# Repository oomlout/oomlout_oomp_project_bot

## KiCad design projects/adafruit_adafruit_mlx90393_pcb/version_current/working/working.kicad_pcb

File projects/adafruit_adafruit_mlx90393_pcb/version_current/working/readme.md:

# Adafruit-MLX90393-PCB by adafruit  
This is a harvested standardized copy of a project from github.  
The original project can be found at:  
https://github.com/adafruit/Adafruit-MLX90393-PCB  
Please consult that link for additional, details, files, and license information.  
Note: It was auto harvested and if the original repo had more than one board file or anything out of the ordinary the files here are likely not representative.

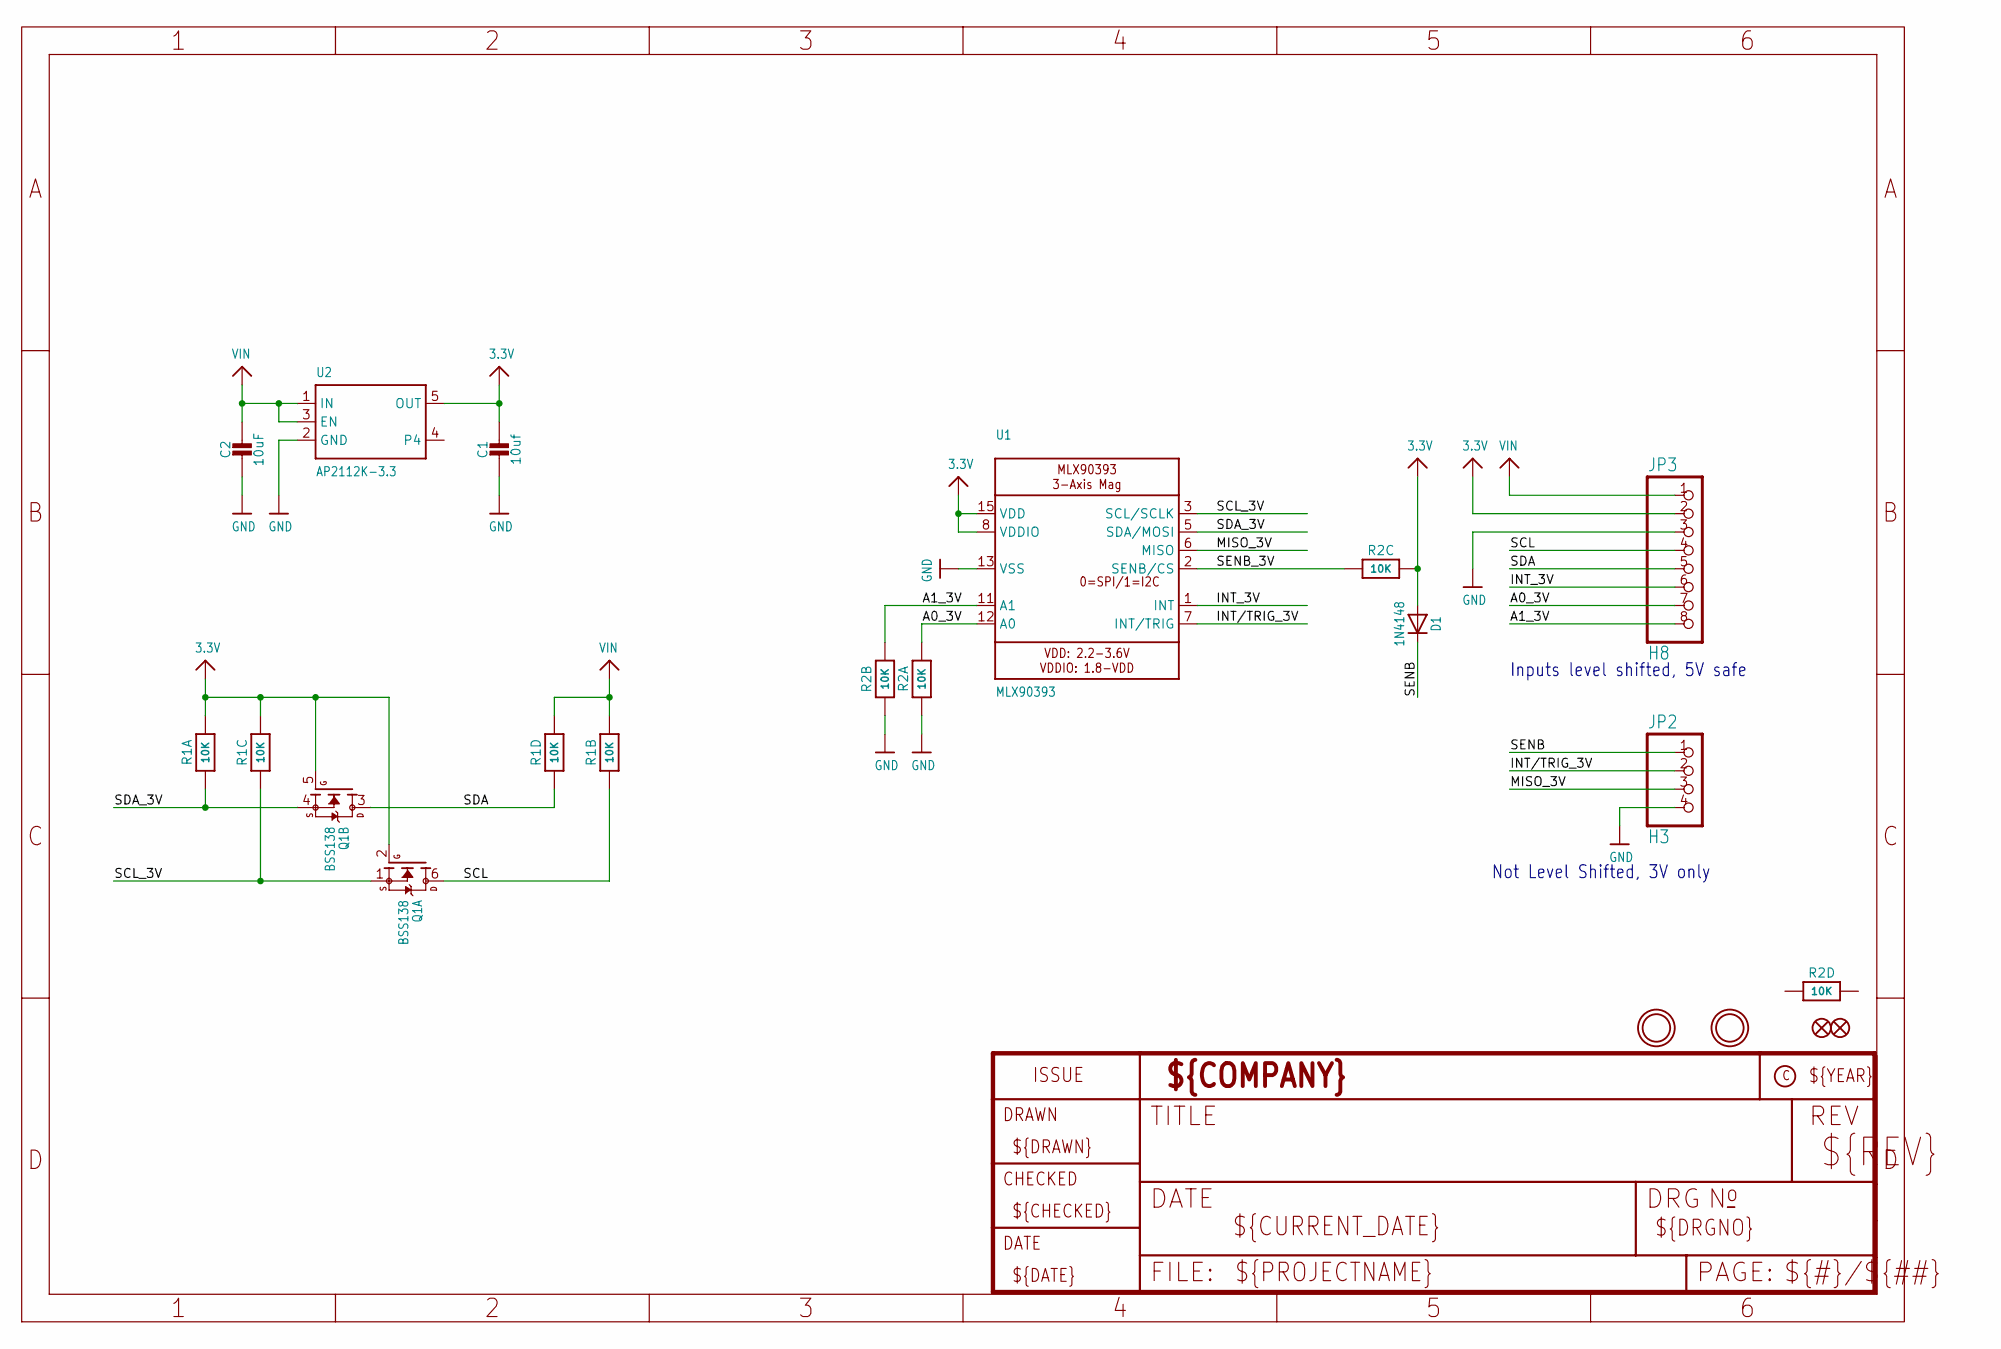
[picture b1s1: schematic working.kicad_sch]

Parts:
C1: 10uf; 0805_10MGAP
C2: 10uF; 0805_10MGAP
D1: 1N4148; SOD-323
FID1, FID3: FIDUCIAL_1MM
JP2: H3; 1X04_ROUND
JP3: H8; 1X08_ROUND
Q1: BSS138; SOT363
R1, R2: 10K; RESPACK_4X0603_NO
U1: MLX90393; QFN16_3MM
U2: AP2112K-3.3; SOT23-5
U$19, U$23: MOUNTINGHOLE2.5; MOUNTINGHOLE_2.5_PLATED

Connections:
3.3V: C1.1, D1.A, JP3.2, Q1.2 (G), Q1.5 (G), R1.6 (2), R1.8 (2), R2.6 (2), U1.8 (VDDIO), U1.15 (VDD), U2.5 (OUT)
A0_3V: JP3.7, R2.8 (2), U1.12 (A0)
A1_3V: JP3.8, R2.7 (2), U1.11 (A1)
GND: C1.2, C2.2, JP2.4, JP3.3, R2.1, R2.2 (1), U1.13 (VSS), U2.2 (GND)
INT/TRIG_3V: JP2.2, U1.7 (INT/TRIG)
INT_3V: JP3.6, U1.1 (INT)
MISO_3V: JP2.3, U1.6 (MISO)
SCL: JP3.4, Q1.6 (D), R1.2 (1)
SCL_3V: Q1.1 (S), R1.3 (1), U1.3 (SCL/SCLK)
SDA: JP3.5, Q1.3 (D), R1.4 (1)
SDA_3V: Q1.4 (S), R1.1, U1.5 (SDA/MOSI)
SENB: D1.C, JP2.1
SENB_3V: R2.3 (1), U1.2 (SENB/CS)
VIN: C2.1, JP3.1, R1.5 (2), R1.7 (2), U2.1 (IN), U2.3 (EN)

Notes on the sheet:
Not Level Shifted, 3V only~{}
Inputs level shifted, 5V safe~{}

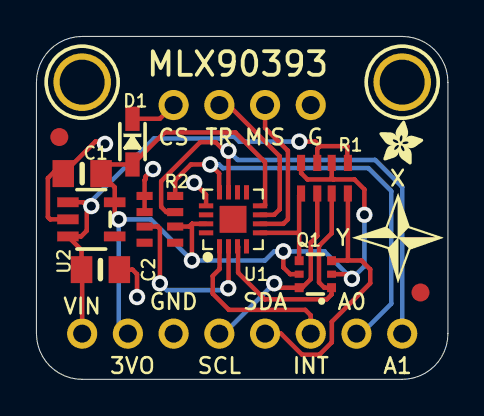
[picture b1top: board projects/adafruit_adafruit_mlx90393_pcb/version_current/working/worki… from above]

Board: 2 copper layers, 22.9 x 19.0 mm, 17 parts (1 on the bottom side), 14 nets.

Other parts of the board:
U$3: SYMBOL_COMPASSXY_5MM
U$18: PCBFEAT-REV-040
U$21: ADAFRUIT_2.5MM

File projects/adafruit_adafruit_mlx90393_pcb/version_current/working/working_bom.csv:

Row,Description,Part,References,Value,Footprint,Quantity Per PCB,Status,Datasheet
1,,CAP_CERAMIC0805_10MGAP,C1 C2,10uf,0805_10MGAP,2, ,
2,,DIODESOD-323,D1,1N4148,SOD-323,1, ,
3,,HEADER-1X4ROUND,JP2,H3,1X04_ROUND,1, ,
4,,HEADER-1X8ROUND,JP3,H8,1X08_ROUND,1, ,
5,,MOSFET-N_DUAL,Q1,BSS138,SOT363,1, ,
6,,RESISTOR_4PACK_NO,R1 R2,10K,RESPACK_4X0603_NO,2, ,
7,,VREG_SOT23-5,U2,AP2112K-3.3,SOT23-5,1, ,
8,,MLX90393,U1,MLX90393,QFN16_3MM,1, ,





Project info:
Schematic:,working
Variant:,default
Revision:,
Date:,2023-08-03_17-21-22
KiCad Version:,7.0.6-7.0.6~ubuntu22.04.1
Statistics:
Component Groups:,8
Component Count:,10 (0 SMD/ 0 THT)
Fitted Components:,10 (0 SMD/ 0 THT)
Number of PCBs:,1
Total Components:,10

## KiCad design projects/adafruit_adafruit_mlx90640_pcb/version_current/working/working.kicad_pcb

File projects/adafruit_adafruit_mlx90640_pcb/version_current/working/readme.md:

# Adafruit-MLX90640-PCB by adafruit  
This is a harvested standardized copy of a project from github.  
The original project can be found at:  
https://github.com/adafruit/Adafruit-MLX90640-PCB  
Please consult that link for additional, details, files, and license information.  
Note: It was auto harvested and if the original repo had more than one board file or anything out of the ordinary the files here are likely not representative.

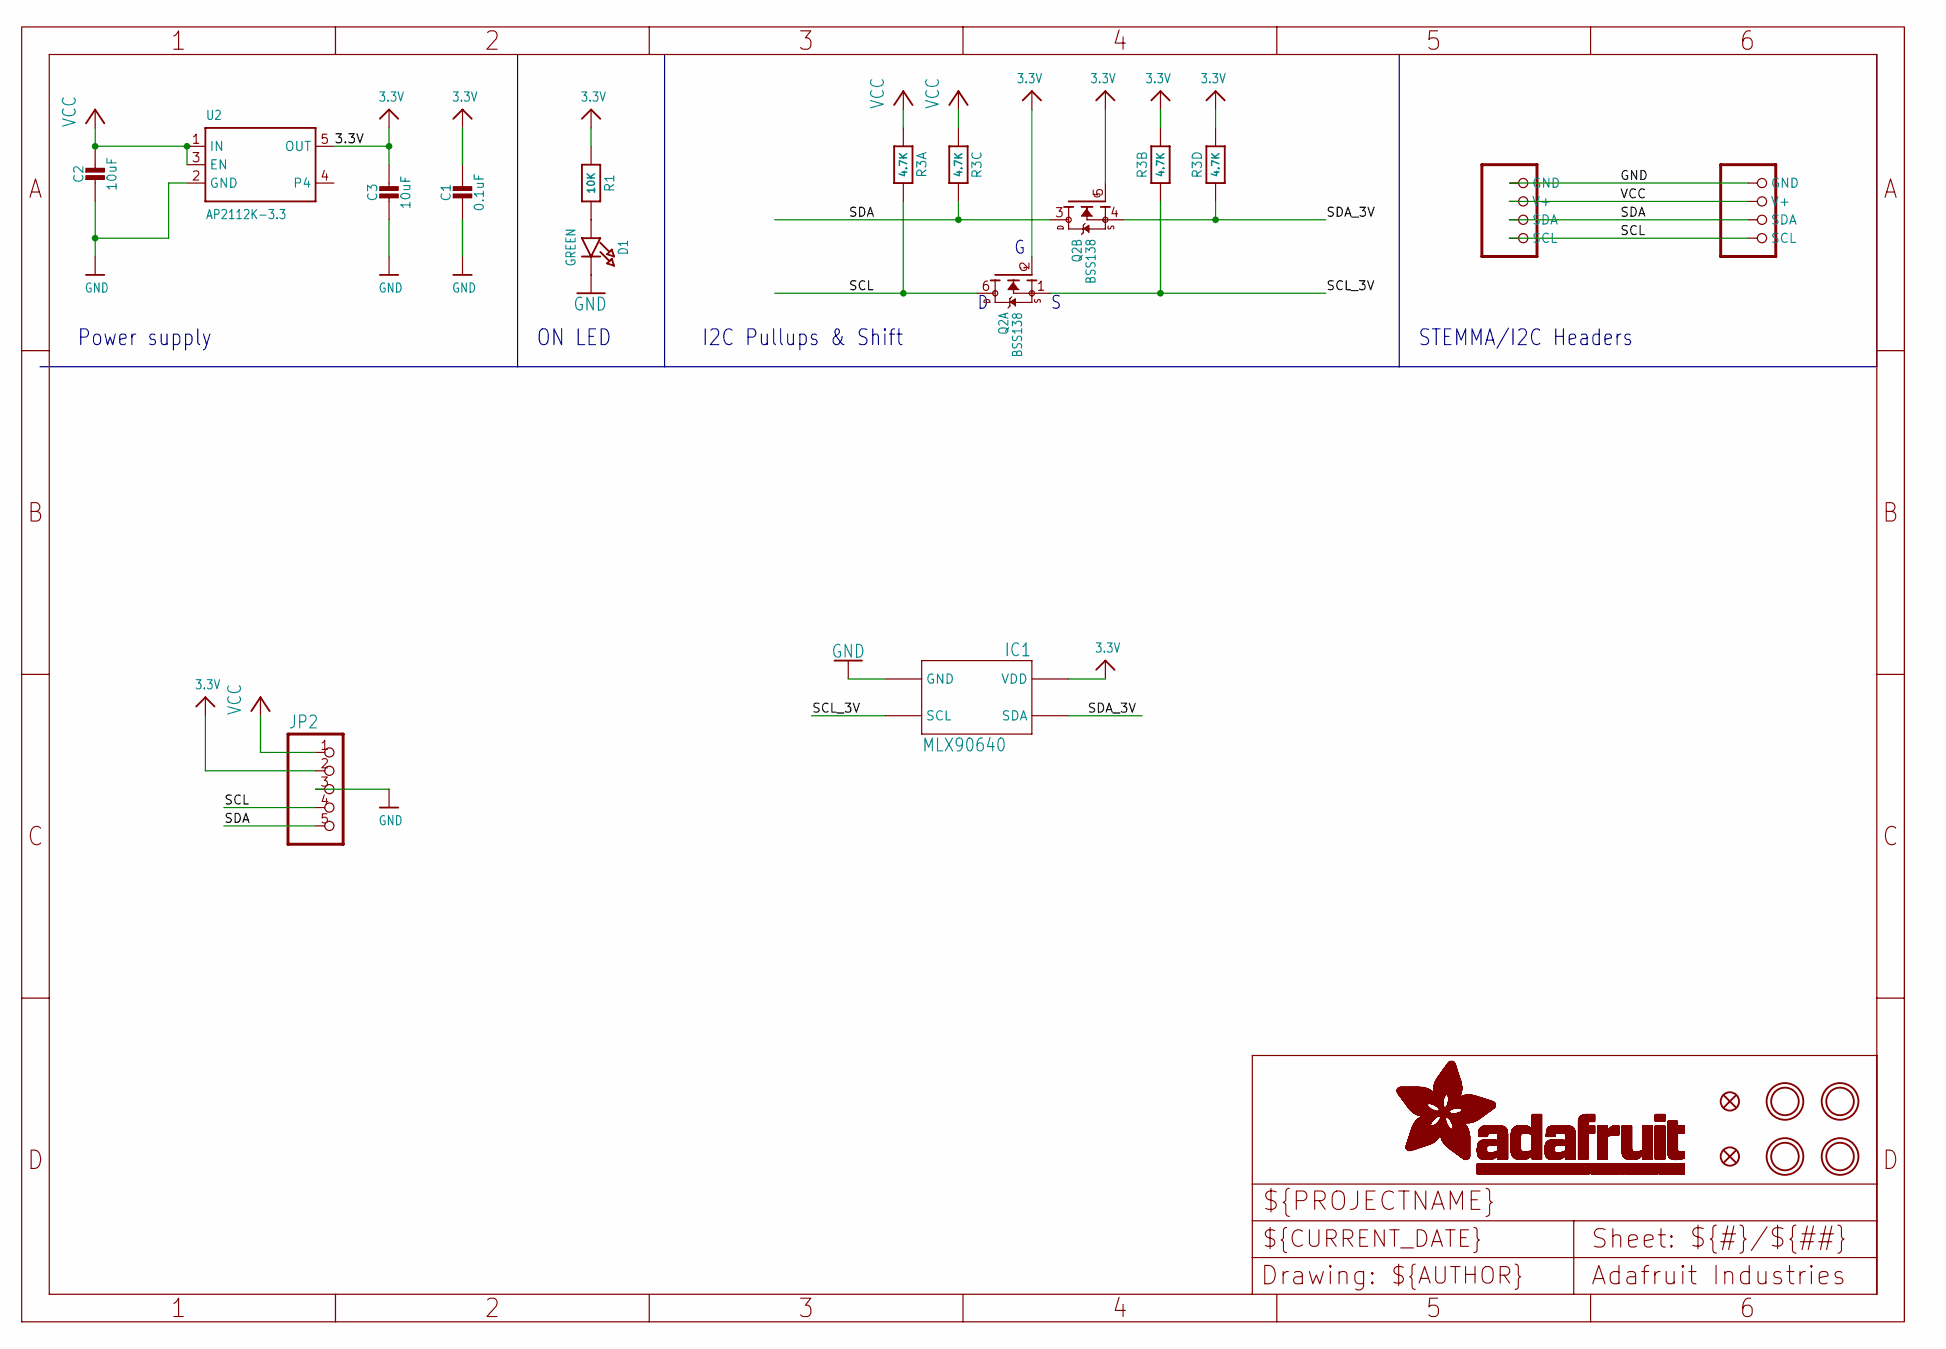
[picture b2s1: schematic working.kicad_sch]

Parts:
C1: 0.1uF; 0603-NO
C2, C3: 10uF; 0805-NO
CONN3, CONN4: STEMMA_I2C_QT; JST_SH4
D1: GREEN; CHIPLED_0603_NOOUTLINE
FID3, FID4: FIDUCIAL_1MM
IC1: MLX90640
JP2: HEADER-1X5ROUND; 1X05_ROUND
Q2: BSS138; SOT363
R1: 10K; 0603-NO
R3: 4.7K; RESPACK_4X0603
U2: AP2112K-3.3; SOT23-5
U$1, U$17, U$19, U$21: MOUNTINGHOLE2.5; MOUNTINGHOLE_2.5_PLATED

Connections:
3.3V: C1.1, C3.1, IC1.VDD, JP2.2, Q2.2 (G), Q2.5 (G), R1.1, R3.2 (1), R3.4 (1), U2.5 (OUT)
GND: C1.2, C2.2, C3.2, CONN3.1 (GND), CONN4.1 (GND), D1.C, IC1.GND, JP2.3, U2.2 (GND)
unnamed: D1.A, R1.2
SCL: CONN3.4 (SCL), CONN4.4 (SCL), JP2.4, Q2.6 (D), R3.8 (2)
SCL_3V: IC1.SCL, Q2.1 (S), R3.7 (2)
SDA: CONN3.3 (SDA), CONN4.3 (SDA), JP2.5, Q2.3 (D), R3.6 (2)
SDA_3V: IC1.SDA, Q2.4 (S), R3.5 (2)
VCC: C2.1, CONN3.2 (V+), CONN4.2 (V+), JP2.1, R3.1, R3.3 (1), U2.1 (IN), U2.3 (EN)

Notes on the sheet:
Power supply
I2C Pullups & Shift
STEMMA/I2C Headers
ON LED

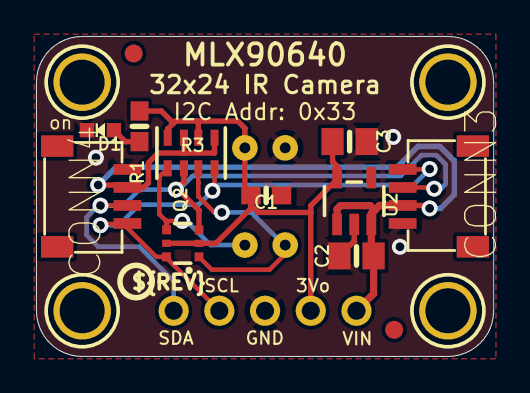
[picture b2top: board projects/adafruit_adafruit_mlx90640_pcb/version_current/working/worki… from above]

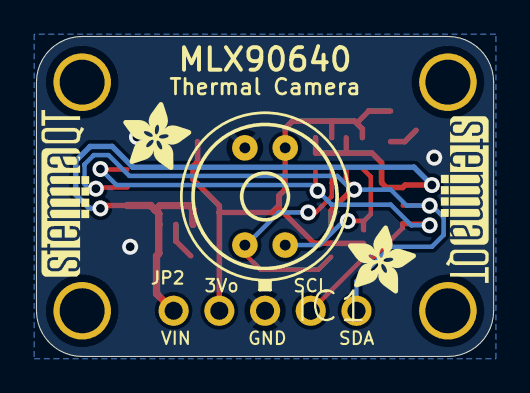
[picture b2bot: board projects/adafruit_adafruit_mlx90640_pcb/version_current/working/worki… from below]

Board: 2 copper layers, 25.4 x 17.8 mm, 23 parts (6 on the bottom side), 8 nets.

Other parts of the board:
U$4, U$22: ADAFRUIT_3.5MM
U$25: PCBFEAT-REV-040
U$30, U$31: STEMMAQT

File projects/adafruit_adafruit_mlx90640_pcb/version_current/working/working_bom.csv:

Row,Description,Part,References,Value,Footprint,Quantity Per PCB,Status,Datasheet
1,,CAP_CERAMIC0603_NO,C1,0.1uF,0603-NO,1, ,
2,,CAP_CERAMIC0805-NOOUTLINE,C2 C3,10uF,0805-NO,2, ,
3,,STEMMA_I2C_QT,CONN3 CONN4,STEMMA_I2C_QT,JST_SH4,2, ,
4,,LED0603_NOOUTLINE,D1,GREEN,CHIPLED_0603_NOOUTLINE,1, ,
5,,MLX90640,IC1,MLX90640,MLX90640,1, ,
6,,HEADER-1X5ROUND,JP2,HEADER-1X5ROUND,1X05_ROUND,1, ,
7,,MOSFET-N_DUAL,Q2,BSS138,SOT363,1, ,
8,,RESISTOR_4PACK,R3,4.7K,RESPACK_4X0603,1, ,
9,,RESISTOR_0603_NOOUT,R1,10K,0603-NO,1, ,
10,,VREG_SOT23-5,U2,AP2112K-3.3,SOT23-5,1, ,





Project info:
Schematic:,working
Variant:,default
Revision:,
Date:,2023-08-03_17-21-22
KiCad Version:,7.0.6-7.0.6~ubuntu22.04.1
Statistics:
Component Groups:,10
Component Count:,12 (0 SMD/ 0 THT)
Fitted Components:,12 (0 SMD/ 0 THT)
Number of PCBs:,1
Total Components:,12

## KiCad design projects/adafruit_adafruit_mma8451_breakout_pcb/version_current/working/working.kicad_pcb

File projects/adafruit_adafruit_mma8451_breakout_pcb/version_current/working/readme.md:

# Adafruit-MMA8451-Breakout-PCB by adafruit  
This is a harvested standardized copy of a project from github.  
The original project can be found at:  
https://github.com/adafruit/Adafruit-MMA8451-Breakout-PCB  
Please consult that link for additional, details, files, and license information.  
Note: It was auto harvested and if the original repo had more than one board file or anything out of the ordinary the files here are likely not representative.

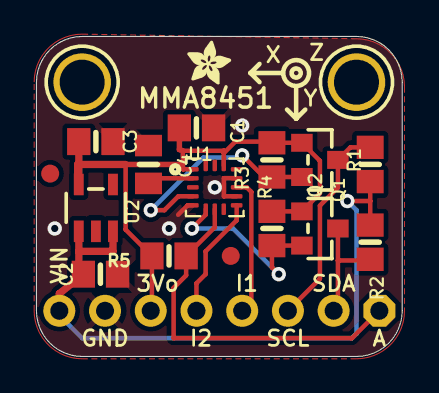
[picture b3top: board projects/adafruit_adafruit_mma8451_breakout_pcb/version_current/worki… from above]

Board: 2 copper layers, 20.3 x 17.8 mm, 19 parts (0 on the bottom side), 11 nets.

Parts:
C1: 0.1uF; 0805-NO
C2, C3: 10uF; 0805-NO
C4: 0.1uF; 0805_10MGAP
FID1, FID2: FIDUCIAL""; FIDUCIAL_1MM
JP1: 1X08_ROUND_70
Q1, Q2: BSS138; SOT23-WIDE
R1, R2, R3, R4, R5: 10K; 0805-NO
U1: MMA8451; MMA845X_QFN_16MM
U2: MIC5225-3.3; SOT23-5
U$3, U$6: MOUNTINGHOLE2.5; MOUNTINGHOLE_2.5_PLATED
U$10: ADAFRUIT_2.5MM

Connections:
+3V3: C1.1, C3.1, JP1.6, Q1.1, Q2.1, R3.2, R4.1, R5.2, U1.1, U1.14, U2.5
GND: C1.2, C2.2, C3.2, C4.2, JP1.7, U1.5, U1.10, U1.12, U2.2
INT1: JP1.4, U1.11
INT2: JP1.5, U1.9
unnamed: C4.1, U1.2
SA0: JP1.1, R5.1, U1.7
SCL: JP1.3, Q1.3, R1.1
SCL_3.3V: Q1.2, R3.1, U1.4
SDA: JP1.2, Q2.3, R2.2
SDA_3.3V: Q2.2, R4.2, U1.6
VIN: C2.1, JP1.8, R1.2, R2.1, U2.1, U2.3

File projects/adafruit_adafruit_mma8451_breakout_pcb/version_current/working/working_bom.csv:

Row,Description,Part,References,Value,Footprint,Quantity Per PCB,Status,Datasheet
1,,CAP_CERAMIC0805-NOOUTLINE,C1,0.1uF,0805-NO,1, ,
2,,CAP_CERAMIC0805_10MGAP,C4,0.1uF,0805_10MGAP,1, ,
3,,CAP_CERAMIC0805-NOOUTLINE,C2 C3,10uF,0805-NO,2, ,
4,,HEADER-1X870MIL,JP1,HEADER-1X870MIL,1X08_ROUND_70,1, ,
5,,MOSFET-NWIDE,Q1 Q2,BSS138,SOT23-WIDE,2, ,
6,,RESISTOR0805_NOOUTLINE,R1 R2 R3 R4 R5,10K,0805-NO,5, ,
7,,VREG_SOT23-5,U2,MIC5225-3.3,SOT23-5,1, ,
8,,ACCEL_MMA845X,U1,MMA8451,MMA845X_QFN_16MM,1, ,





Project info:
Schematic:,working
Variant:,default
Revision:,
Date:,2023-08-03_17-21-22
KiCad Version:,7.0.6-7.0.6~ubuntu22.04.1
Statistics:
Component Groups:,8
Component Count:,14 (0 SMD/ 0 THT)
Fitted Components:,14 (0 SMD/ 0 THT)
Number of PCBs:,1
Total Components:,14

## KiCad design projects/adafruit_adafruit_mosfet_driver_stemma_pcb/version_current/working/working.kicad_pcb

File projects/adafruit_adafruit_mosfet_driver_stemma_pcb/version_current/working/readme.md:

# Adafruit-MOSFET-Driver-STEMMA-PCB by adafruit  
This is a harvested standardized copy of a project from github.  
The original project can be found at:  
https://github.com/adafruit/Adafruit-MOSFET-Driver-STEMMA-PCB  
Please consult that link for additional, details, files, and license information.  
Note: It was auto harvested and if the original repo had more than one board file or anything out of the ordinary the files here are likely not representative.

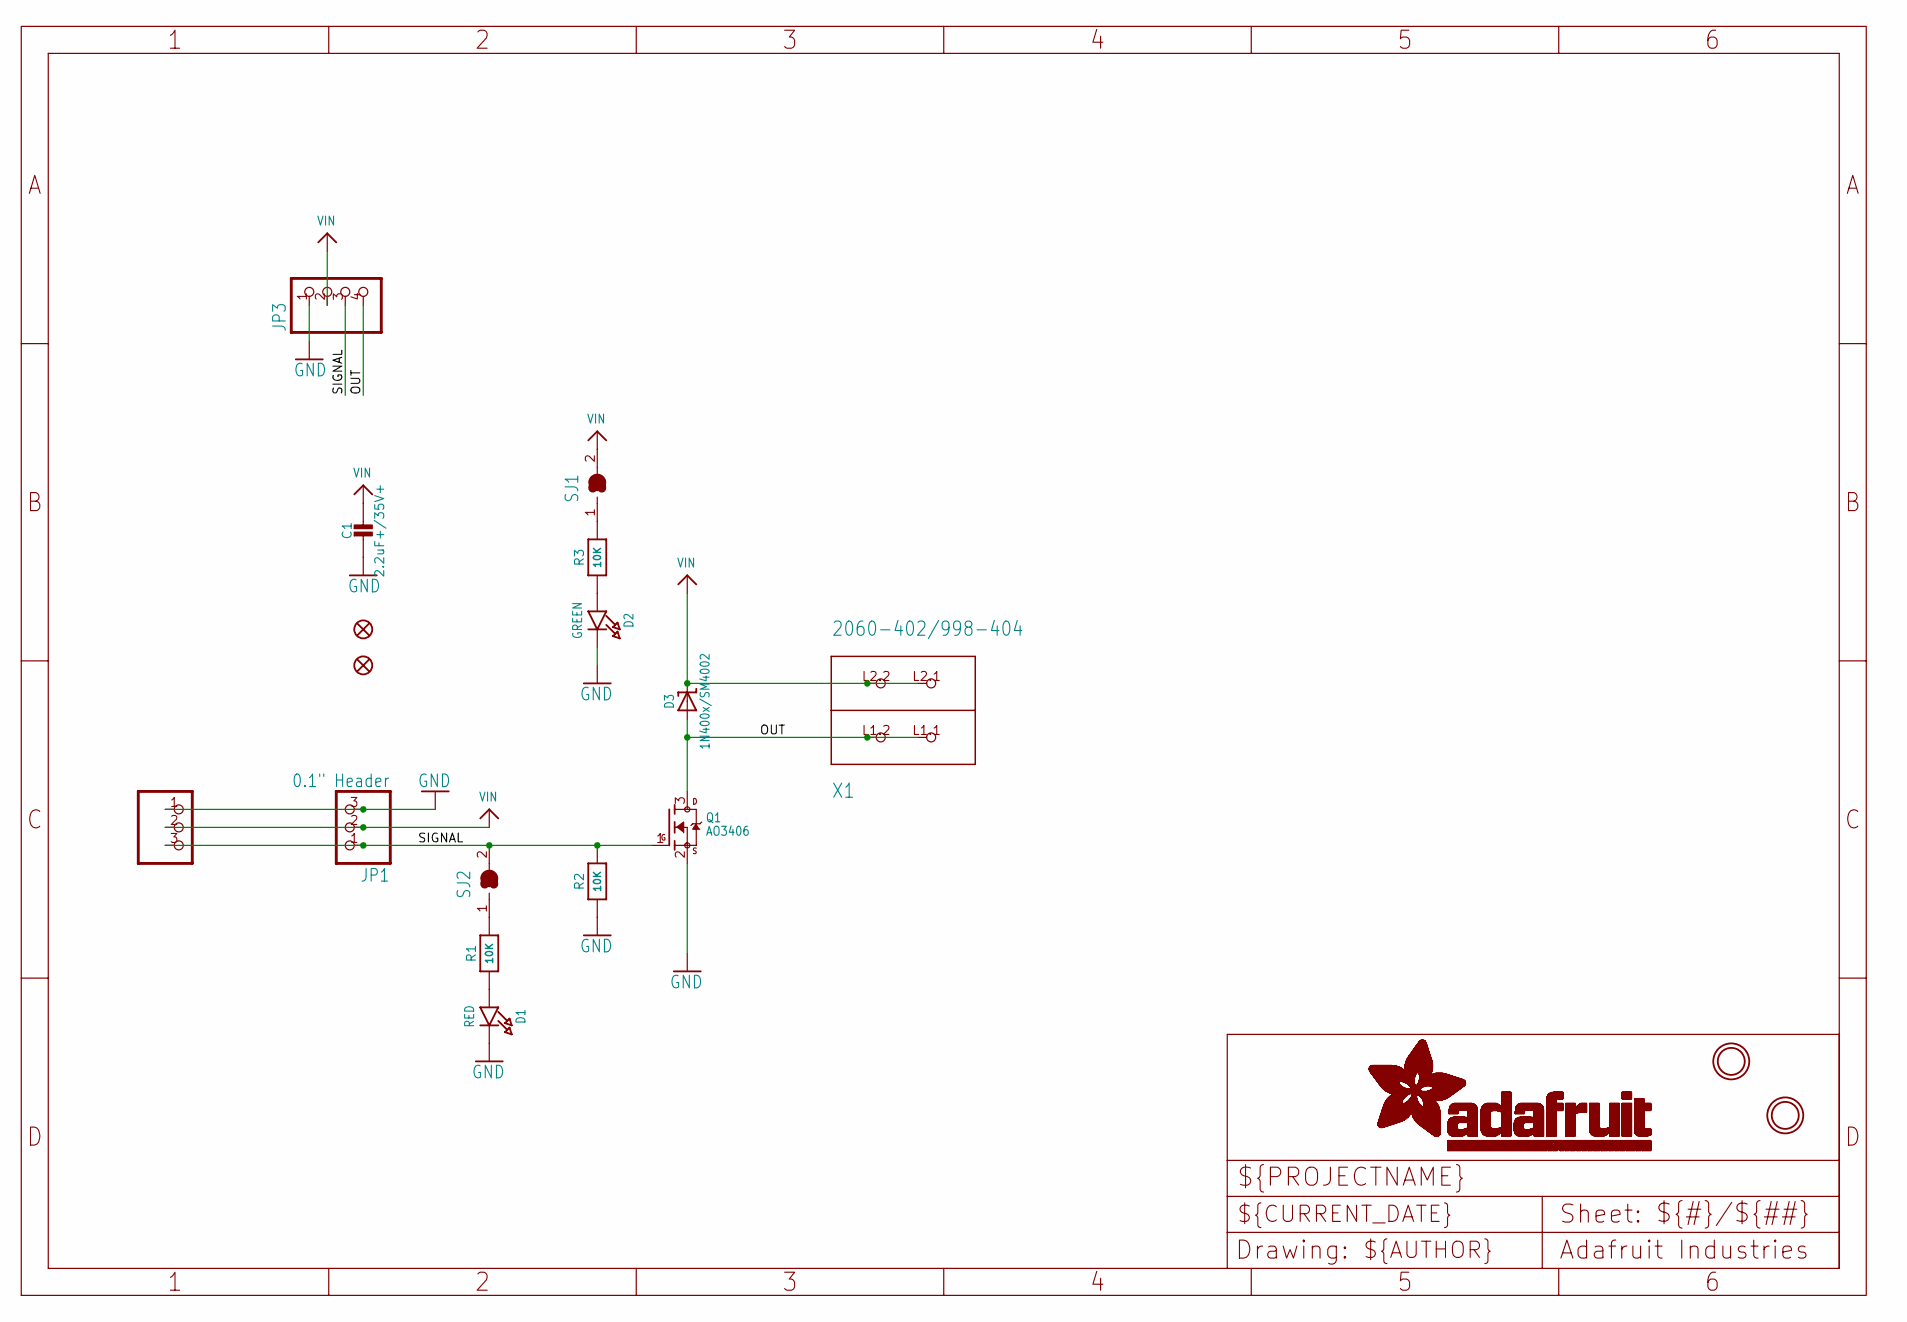
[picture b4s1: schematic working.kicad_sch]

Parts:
C1: 2.2uF+/35V+; 0805-NO
D1: RED; CHIPLED_0603_NOOUTLINE
D2: GREEN; CHIPLED_0603_NOOUTLINE
D3: 1N400x/SM4002; SOD-123
FID2, FID3: FIDUCIAL_1MM
JP1: 0.1" Header; 1X03_OVAL
JP3: HEADER-1X4ROUND; 1X04_ROUND
Q1: AO3406; SOT23-WIDE
R1, R2, R3: 10K; 0603-NO
SJ1, SJ2: SOLDERJUMPER_CLOSED; SOLDERJUMPER_CLOSEDWIRE
U$1, U$8: MOUNTINGHOLE2.5; MOUNTINGHOLE_2.5_PLATED
X1: 2060-402/998-404; P-2060-402_998-404
X4: JST PH 3; JSTPH3

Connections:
GND: C1.2, D1.C, D2.C, JP1.3, JP3.1, Q1.2 (S), R2.1, X4.1
unnamed: R3.2, SJ1.1
unnamed: D1.A, R1.1
unnamed: R1.2, SJ2.1
unnamed: D2.A, R3.1
OUT: D3.A, JP3.4, Q1.3 (D), X1.L1.1 (P1.1), X1.L1.2 (P1.2)
SIGNAL: JP1.1, JP3.3, Q1.1 (G), R2.2, SJ2.2, X4.3
VIN: C1.1, D3.C, JP1.2, JP3.2, SJ1.2, X1.L2.1 (P2.1), X1.L2.2 (P2.2), X4.2

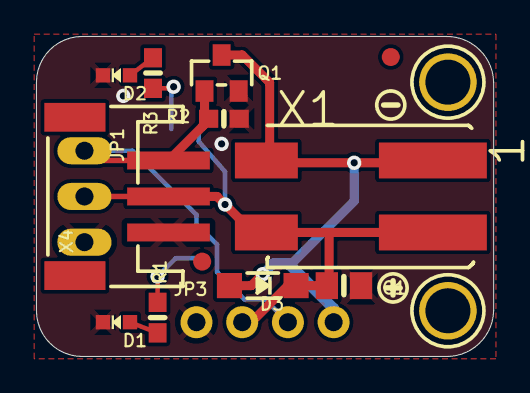
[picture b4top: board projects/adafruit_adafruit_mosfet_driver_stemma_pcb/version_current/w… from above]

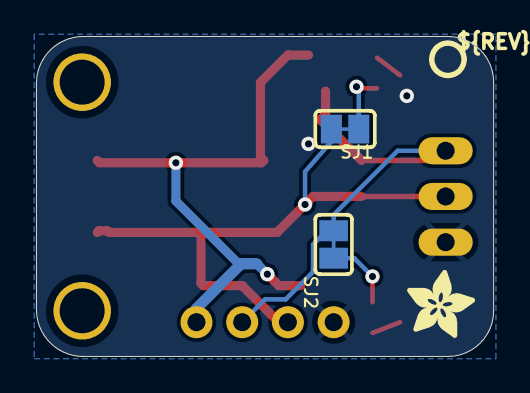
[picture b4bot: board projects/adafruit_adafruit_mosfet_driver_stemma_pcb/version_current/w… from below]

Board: 16 copper layers, 25.4 x 17.8 mm, 36 parts (15 on the bottom side), 8 nets.

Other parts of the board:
PLABEL0: PLABEL0
PLABEL1: PLABEL1
PLABEL2: PLABEL2
PLABEL3: PLABEL3
PLABEL4: PLABEL4
PLABEL5: PLABEL5
PLABEL6: PLABEL6
PLABEL7: PLABEL7
PLABEL8: PLABEL8
PLABEL9: PLABEL9
PLABEL10: PLABEL10
PLABEL11: PLABEL11
PLABEL12: PLABEL12
PLABEL13: PLABEL13
U$3: SYMBOL_PLUS
U$5: PCBFEAT-REV-040
U$9: SYMBOL_MINUS
U$12: ADAFRUIT_3.5MM

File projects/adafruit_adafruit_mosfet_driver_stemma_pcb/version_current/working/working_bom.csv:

Row,Description,Part,References,Value,Footprint,Quantity Per PCB,Status,Datasheet
1,,CAP_CERAMIC0805-NOOUTLINE,C1,2.2uF+/35V+,0805-NO,1, ,
2,,DIODE-SCHOTTKYSOD-123,D3,1N400x/SM4002,SOD-123,1, ,
3,,LED0603_NOOUTLINE,D2,GREEN,CHIPLED_0603_NOOUTLINE,1, ,
4,,LED0603_NOOUTLINE,D1,RED,CHIPLED_0603_NOOUTLINE,1, ,
5,,HEADER-1X3,JP1,"0.1"" Header",1X03_OVAL,1, ,
6,,HEADER-1X4ROUND,JP3,HEADER-1X4ROUND,1X04_ROUND,1, ,
7,,MOSFET-NWIDE,Q1,AO3406,SOT23-WIDE,1, ,
8,,RESISTOR_0603_NOOUT,R1 R2 R3,10K,0603-NO,3, ,
9,,2060-402/998-404,X1,2060-402/998-404,P-2060-402_998-404,1, ,
10,,CON_JST_PH_3PIN,X4,JST PH 3,JSTPH3,1, ,





Project info:
Schematic:,working
Variant:,default
Revision:,
Date:,2023-08-03_17-21-22
KiCad Version:,7.0.6-7.0.6~ubuntu22.04.1
Statistics:
Component Groups:,10
Component Count:,12 (0 SMD/ 0 THT)
Fitted Components:,12 (0 SMD/ 0 THT)
Number of PCBs:,1
Total Components:,12

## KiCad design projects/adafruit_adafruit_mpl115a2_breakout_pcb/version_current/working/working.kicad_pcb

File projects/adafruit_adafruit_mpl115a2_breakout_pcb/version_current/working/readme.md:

# Adafruit-MPL115A2-Breakout-PCB by adafruit  
This is a harvested standardized copy of a project from github.  
The original project can be found at:  
https://github.com/adafruit/Adafruit-MPL115A2-Breakout-PCB  
Please consult that link for additional, details, files, and license information.  
Note: It was auto harvested and if the original repo had more than one board file or anything out of the ordinary the files here are likely not representative.

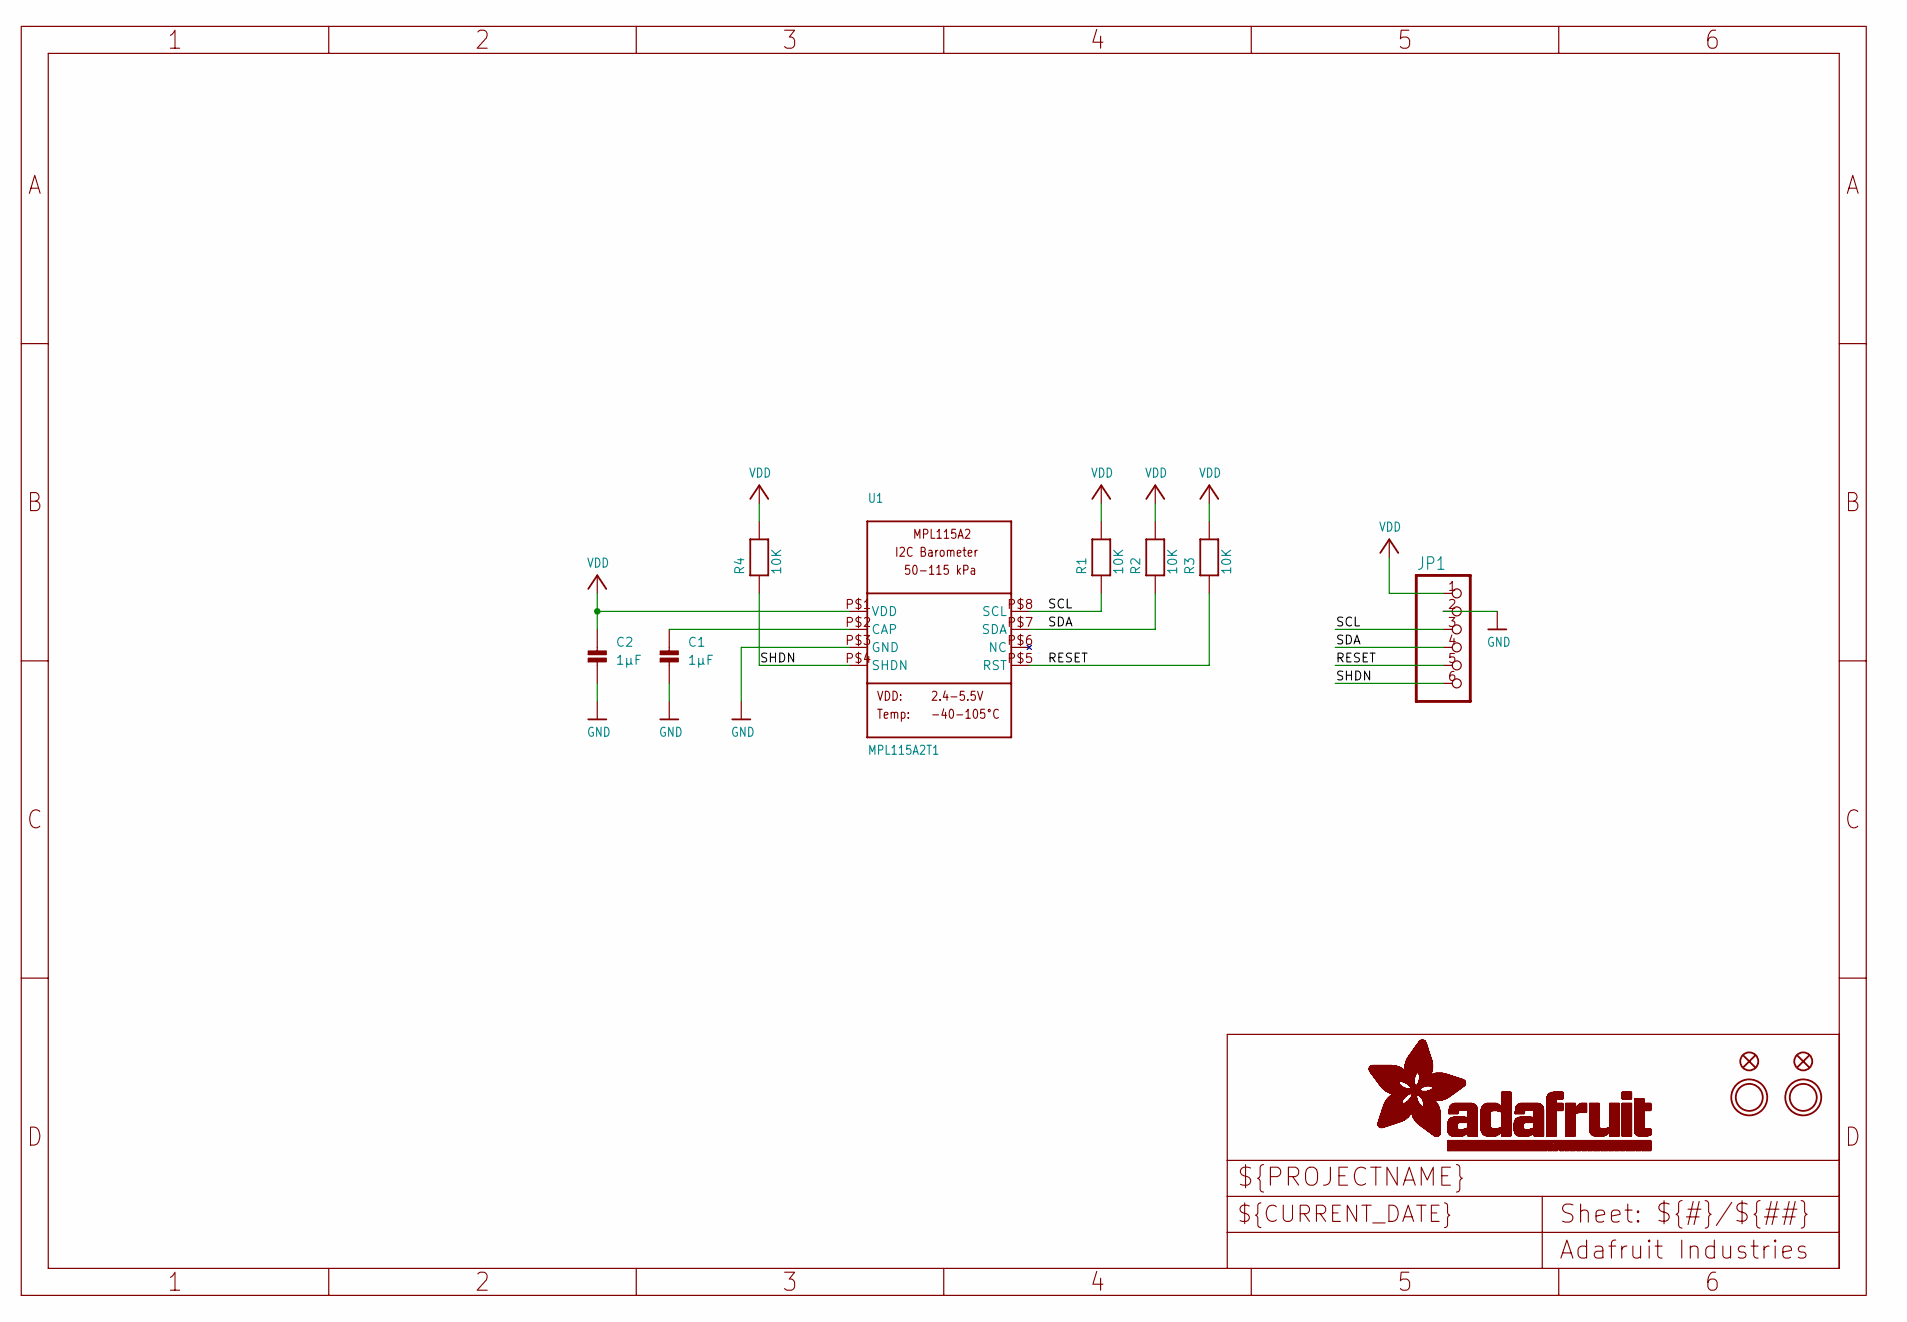
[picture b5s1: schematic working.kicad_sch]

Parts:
C1, C2: 1µF; 0805
FID1, FID2: FIDUCIAL""; FIDUCIAL_1MM
JP1: HEADER-1X670MIL; 1X06_ROUND_70
R1, R2, R3, R4: 10K; 0805
U1: MPL115A2T1; LGA8
U$8, U$9: MOUNTINGHOLE2.5; MOUNTINGHOLE_2.5_PLATED

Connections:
GND: C1.2, C2.2, JP1.2, U1.P$3 (GND)
unnamed: C1.1, U1.P$2 (CAP)
RESET: JP1.5, R3.1, U1.P$5 (RST)
SCL: JP1.3, R1.1, U1.P$8 (SCL)
SDA: JP1.4, R2.1, U1.P$7 (SDA)
SHDN: JP1.6, R4.1, U1.P$4 (SHDN)
VDD: C2.1, JP1.1, R1.2, R2.2, R3.2, R4.2, U1.P$1 (VDD)

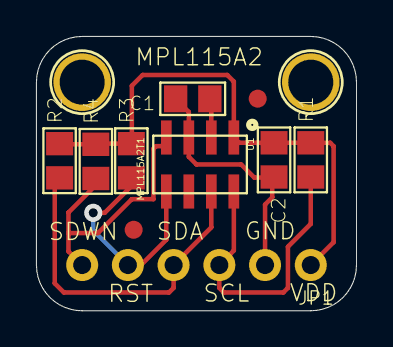
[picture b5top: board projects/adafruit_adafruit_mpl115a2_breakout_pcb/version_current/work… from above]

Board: 2 copper layers, 17.8 x 15.2 mm, 13 parts (1 on the bottom side), 7 nets.

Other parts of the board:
U$14: ADAFRUIT_3.5MM
